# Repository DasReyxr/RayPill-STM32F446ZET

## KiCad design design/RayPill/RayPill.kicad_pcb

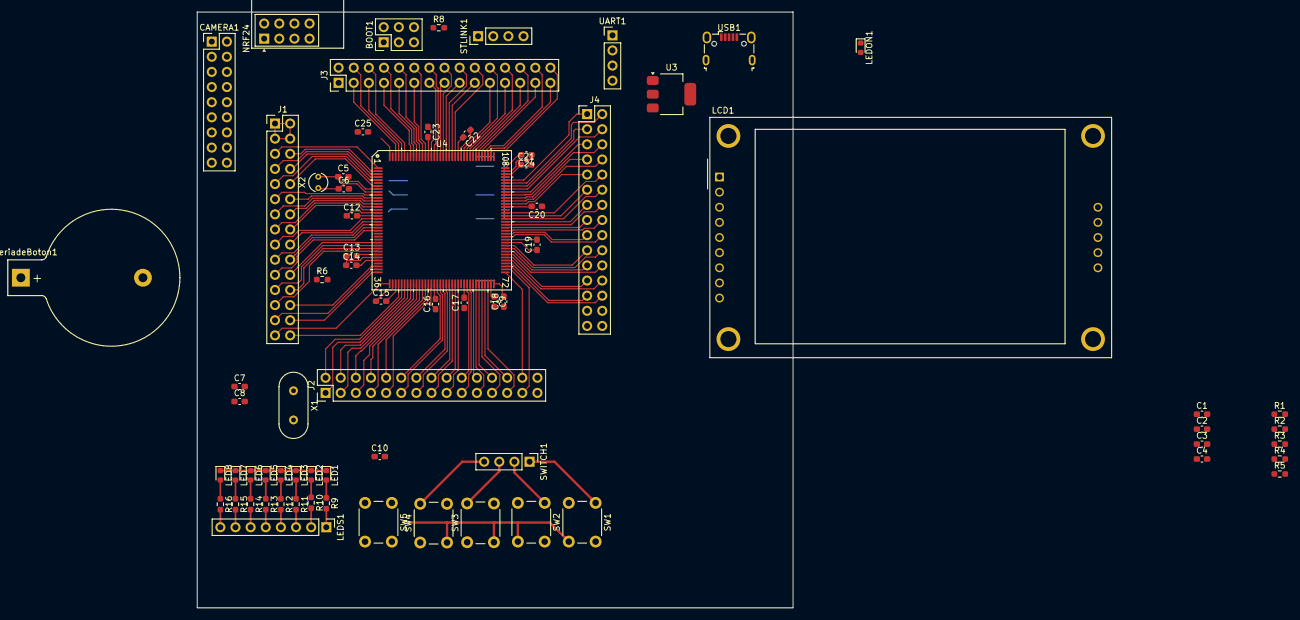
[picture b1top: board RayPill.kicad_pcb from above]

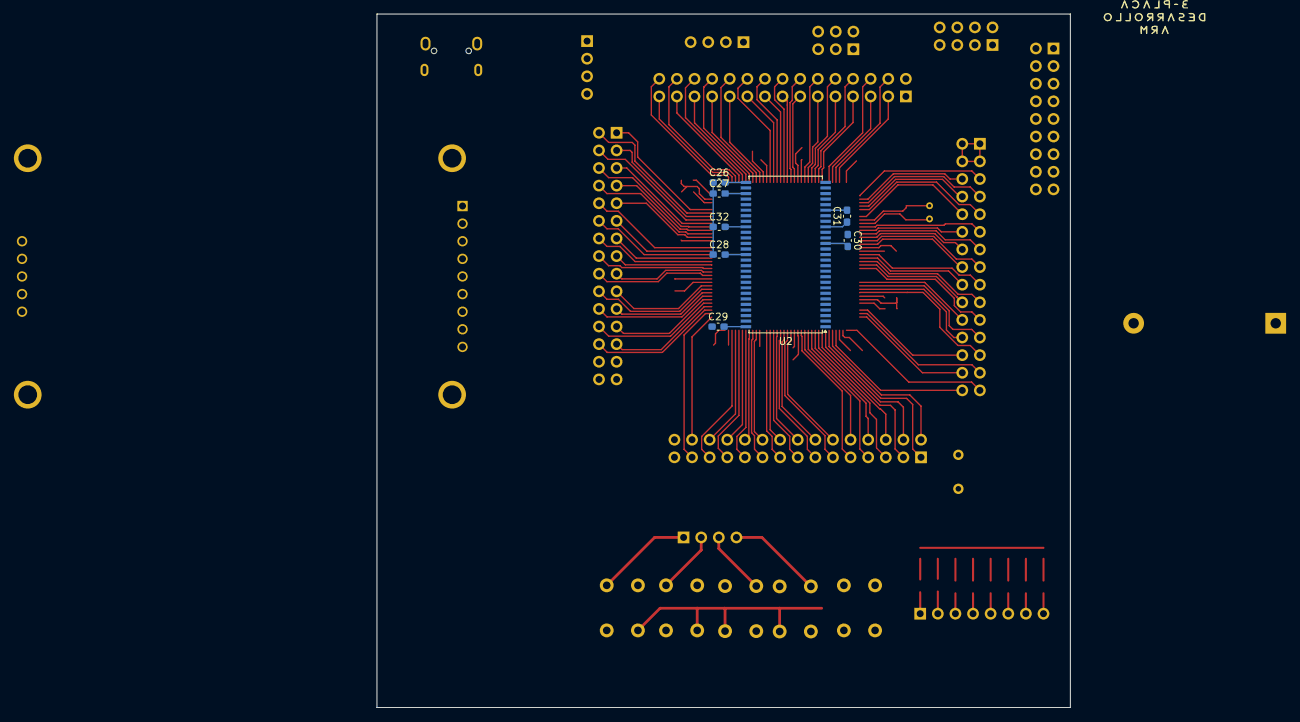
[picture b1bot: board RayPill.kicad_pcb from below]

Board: 2 copper layers, 100.0 x 100.0 mm, 80 parts (9 on the bottom side), 149 nets.

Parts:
BOOT1: Conn_02x03_Odd_Even; PinHeader_2x03_P2.54mm_Vertical
BateriadeBoton1: Portapila; BatteryHolder_Keystone_103_1x20mm
C1, C2: 10uF; C_0603_1608Metric_Pad1.08x0.95mm_HandSolder
C3, C4, C10, C12, C13, C14, C15, C16, C17, C18, C19, C20, C22, C23, C24, C25, C26, C27, C28, C29, C30, C31, C32: 100nF; C_0603_1608Metric_Pad1.08x0.95mm_HandSolder
C5, C6: 12p; C_0603_1608Metric_Pad1.08x0.95mm_HandSolder
C7, C8: 8p; C_0603_1608Metric_Pad1.08x0.95mm_HandSolder
C9: 2.2u; C_0603_1608Metric_Pad1.08x0.95mm_HandSolder
C21: 2.2uF; C_0603_1608Metric_Pad1.08x0.95mm_HandSolder
CAMERA1: Conn_02x09_Odd_Even; PinHeader_2x09_P2.54mm_Vertical
J1, J3, J4: Conn_02x15_Top_Bottom; PinHeader_2x15_P2.54mm_Vertical
J2: Conn_02x15_Odd_Even; PinHeader_2x15_P2.54mm_Vertical
LCD1: Conn_01x14; CR2013-MI2120
LED1, LED2, LED3, LED4, LED5, LED6, LED7, LED8: AZUL; LED_0603_1608Metric
LEDON1: ROJO; LED_0603_1608Metric
LEDS1: Conn_01x08; PinHeader_1x08_P2.54mm_Vertical
LOGO: LOGO; 3-LogoArm
NRF24: Conn_02x04_Odd_Even; nRF24L01_Breakout
R1, R2: 22; R_0603_1608Metric_Pad0.98x0.95mm_HandSolder
R3, R6, R8: 10k; R_0603_1608Metric_Pad0.98x0.95mm_HandSolder
R4, R9, R10, R11, R12, R13, R14, R15, R16: 220; R_0603_1608Metric_Pad0.98x0.95mm_HandSolder
R5: 0; R_0603_1608Metric_Pad0.98x0.95mm_HandSolder
STLINK1: Conn_01x04; PinHeader_1x04_P2.54mm_Vertical
SW1, SW2, SW3, SW4, SW5: SW_Push; SW_PUSH_6mm_H4.3mm
SWITCH1: Conn_01x04; PinHeader_1x04_P2.54mm_Vertical
U2: IS42S16400J-xT; TSOP-II-54_22.2x10.16mm_P0.8mm
U3: LM317_SOT-223; SOT-223-3_TabPin2
U4: STM32F446ZET7; LQFP-144_20x20mm_P0.5mm
UART1: Conn_01x04; PinHeader_1x04_P2.54mm_Vertical
USB1: USB_B_Mini; USB_Micro-B_Wuerth_629105150521
X1: 8MHz; Crystal_HC18-U_Vertical
X2: 32.768KHz; Crystal_C38-LF_D3.0mm_L8.0mm_Vertical

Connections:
+5V: C1.2, C3.2, R3.2, U3.3 (VI), USB1.1 (VBUS)
/28/U2: U2.28 (GND), U2.41 (GND), U2.54 (GND)
/33: R5.1, U4.33 (VDDA)
/BOOT0: BOOT1.3, U4.138 (BOOT0)
/BOOT1(PB2): J2.7, R8.2, U4.48 (PB2-BOOT1)
/PA0: J1.26, U4.34 (PA0-WKUP)
/PA1: J1.27, U4.35 (PA1)
/PA2: J1.28, U4.36 (PA2)
/PA3: J1.29, U4.37 (PA3)
/PA4: CAMERA1.6, J1.30, U4.40 (PA4)
/PA5: J2.2, LCD1.8, U4.41 (PA5)
/PA6: CAMERA1.7, J2.1, U4.42 (PA6)
/PA7: J2.4, LCD1.9, U4.43 (PA7)
/PA8: CAMERA1.8, J4.5, U4.100 (PA8)
/PA9: J4.4, U4.101 (PA9), UART1.2
/PA10: J4.3, U4.102 (PA10), UART1.3
/PA11: J4.2, U4.103 (PA11)
/PA12: J4.1, U4.104 (PA12)
/PA15: J3.30, U4.110 (PA15)
/PB0: J2.5, U4.46 (PB0)
/PB1: J2.8, U4.47 (PB1)
/PB3: J3.11, U4.133 (PB3)
/PB4: J3.10, LCD1.6, U4.134 (PB4)
/PB5: J3.9, U2.37 (CKE), U4.135 (PB5)
/PB6: J3.8, U2.19 (~CS), U4.136 (PB6)
/PB7: CAMERA1.5, J3.7, U4.137 (PB7)
/PB8: CAMERA1.3, J3.6, U4.139 (PB8)
/PB9: CAMERA1.4, J3.5, U4.140 (PB9)
/PB10: J2.26, U4.69 (PB10)
/PB11: J2.25, U4.70 (PB11)
/PB12: J2.28, U4.73 (PB12)
/PB13: J2.27, U4.74 (PB13)
/PB14: J4.26, R1.1, U4.75 (PB14)
/PB15: J4.25, R2.2, U4.76 (PB15)
/PC0: J1.22, U2.16 (~WE), U4.26 (PC0)
/PC1: J1.23, U4.27 (PC1)
/PC2: J1.24, U4.28 (PC2)
/PC3: J1.25, U4.29 (PC3)
/PC4: J2.3, U4.44 (PC4)
/PC5: J2.6, U4.45 (PC5)
/PC6: CAMERA1.16, J4.9, U4.96 (PC6)
/PC7: CAMERA1.15, J4.8, U4.97 (PC7)
/PC8: CAMERA1.14, J4.7, U4.98 (PC8)
/PC9: J4.6, U4.99 (PC9)
/PC10: J3.29, LCD1.5, NRF24.5, U4.111 (PC10)
/PC11: J3.28, LCD1.2, NRF24.7, U4.112 (PC11)
/PC12: J3.27, LCD1.3, NRF24.6, U4.113 (PC12)
/PC13: J1.10, U4.7 (PC13)
/PD0: J3.26, U2.5 (DQ2), U4.114 (PD0)
/PD1: J3.25, U2.7 (DQ3), U4.115 (PD1)
/PD2: J3.24, LCD1.12, U4.116 (PD2)
/PD3: CAMERA1.11, J3.23, U4.117 (PD3)
/PD4: J3.22, LCD1.11, U4.118 (PD4)
/PD5: J3.21, LCD1.10, U4.119 (PD5)
/PD6: J3.20, LCD1.7, U4.122 (PD6)
/PD7: J3.19, LCD1.4, U4.123 (PD7)
/PD8: J4.24, U2.50 (DQ13), U4.77 (PD8)
/PD9: J4.23, U2.51 (DQ14), U4.78 (PD9)
/PD10: J4.22, U2.53 (DQ15), U4.79 (PD10)
/PD11: J4.21, U4.80 (PD11)
/PD12: J4.20, U4.81 (PD12)
/PD13: J4.19, U4.82 (PD13)
/PD14: J4.18, U2.2 (DQ0), U4.85 (PD14)
/PD15: J4.17, U2.4 (DQ1), U4.86 (PD15)
/PE0: J3.4, U2.15 (LDQM), U4.141 (PE0)
/PE1: J3.3, U2.39 (UDQM), U4.142 (PE1)
/PE2: J1.5, U4.1 (PE2)
/PE3: J1.6, U4.2 (PE3)
/PE4: CAMERA1.12, J1.7, U4.3 (PE4)
/PE5: CAMERA1.10, J1.8, U4.4 (PE5)
/PE6: CAMERA1.9, J1.9, U4.5 (PE6)
/PE7: J2.15, U2.8 (DQ4), U4.58 (PE7)
/PE8: J2.18, U2.10 (DQ5), U4.59 (PE8)
/PE9: J2.17, U2.11 (DQ6), U4.60 (PE9)
/PE10: J2.20, U2.13 (DQ7), U4.63 (PE10)
/PE11: J2.19, U2.42 (DQ8), U4.64 (PE11)
/PE12: J2.22, U2.44 (DQ9), U4.65 (PE12)
/PE13: J2.21, U2.45 (DQ10), U4.66 (PE13)
/PE14: J2.24, U2.47 (DQ11), U4.67 (PE14)
/PE15: J2.23, U2.48 (DQ12), U4.68 (PE15)
/PF0: J1.11, U2.23 (A0), U4.10 (PF0)
/PF1: J1.12, U2.24 (A1), U4.11 (PF1)
/PF2: J1.13, U2.25 (A2), U4.12 (PF2)
/PF3: J1.14, U2.26 (A3), U4.13 (PF3)
/PF4: J1.15, U2.29 (A4), U4.14 (PF4)
/PF5: J1.16, U2.30 (A5), U4.15 (PF5)
/PF6: J1.17, U4.18 (PF6)
/PF7: J1.18, U4.19 (PF7)
/PF8: J1.19, U4.20 (PF8)
/PF9: J1.20, U4.21 (PF9)
/PF10: J1.21, U4.22 (PF10)
/PF11: J2.10, U2.18 (~RAS), U4.49 (PF11)
/PF12: J2.9, U2.31 (A6), U4.50 (PF12)
/PF13: J2.12, U2.32 (A7), U4.53 (PF13)
/PF14: J2.11, U2.33 (A8), U4.54 (PF14)
/PF15: J2.14, U2.34 (A9), U4.55 (PF15)
/PG0: J2.13, U2.22 (A10), U4.56 (PG0)
/PG1: J2.16, U2.35 (A11), U4.57 (PG1)
/PG2: J4.16, U4.87 (PG2)
/PG3: J4.15, U4.88 (PG3)
/PG4: J4.14, U2.20 (BA0), U4.89 (PG4)
/PG5: J4.13, U2.21 (BA1), U4.90 (PG5)
/PG6: J4.12, U4.91 (PG6)
/PG7: J4.11, U4.92 (PG7)
/PG8: J4.10, U2.38 (CLK), U4.93 (PG8)
/PG9: J3.18, LCD1.1, U4.124 (PG9)
/PG10: J3.17, NRF24.3, U4.125 (PG10)
/PG11: CAMERA1.13, J3.16, U4.126 (PG11)
/PG12: J3.15, NRF24.4, U4.127 (PG12)
/PG13: J3.14, NRF24.8, U4.128 (PG13)
/PG14: J3.13, U4.129 (PG14)
/PG15: J3.12, U2.17 (~CAS), U4.132 (PG15)
/RES: C10.2, R6.2, SW5.2, U4.25 (NRST)
/SWCLK: STLINK1.2, U4.109 (PA14)
/SWDIO: STLINK1.3, U4.105 (PA13)
/VBAT: BateriadeBoton1.1, U4.6 (VBAT)
Earth: BateriadeBoton1.2, C1.1, C2.1, C3.1, C4.1, LCD1.13, LEDON1.1 (K), STLINK1.4, U3.1 (ADJ), UART1.4, USB1.5 (GND)
GND: BOOT1.5, BOOT1.6, C5.2, C6.2, C7.2, C8.2, C9.2, C10.1, C12.1, C13.1, C14.1, C15.1, C16.1, C17.1, C18.1, C19.1, C20.1, C21.2, C22.1, C23.1, C24.1, C25.1, C26.1, C27.1, C28.1, C29.1, C30.1, C31.1, C32.1, CAMERA1.2, J2.29, J2.30, J4.27, J4.28, J4.29, J4.30, LED1.1 (K), LED2.1 (K), LED3.1 (K), LED4.1 (K), LED5.1 (K), LED6.1 (K), LED7.1 (K), LED8.1 (K), NRF24.1, SW1.2, SW2.2, SW3.2, SW4.2, SW5.1, U2.6 (GNDQ), U2.12 (GNDQ), U2.46 (GNDQ), U2.52 (GNDQ), U4.16 (VSS), U4.31 (VSSA), U4.38 (VSS), U4.51 (VSS), U4.61 (VSS), U4.83 (VSS), U4.94 (VSS), U4.107 (VSS), U4.120 (VSS), U4.130 (VSS)
unnamed: BOOT1.4, R8.1
unnamed: LED1.2 (A), R9.1
unnamed: LED2.2 (A), R10.1
unnamed: LED3.2 (A), R11.1
unnamed: LED4.2 (A), R12.1
unnamed: LED5.2 (A), R13.1
unnamed: LED6.2 (A), R14.1
unnamed: LED7.2 (A), R15.1
unnamed: LED8.2 (A), R16.1
unnamed: LEDON1.2 (A), R4.2
unnamed: LEDS1.1, R9.2
unnamed: LEDS1.2, R10.2
unnamed: LEDS1.3, R11.2
unnamed: LEDS1.4, R12.2
unnamed: LEDS1.5, R13.2
unnamed: LEDS1.6, R14.2
unnamed: LEDS1.7, R15.2
unnamed: LEDS1.8, R16.2
unnamed: SW1.1, SWITCH1.1
unnamed: SW2.1, SWITCH1.2
unnamed: SW3.1, SWITCH1.3
unnamed: SW4.1, SWITCH1.4
unnamed: C5.1, U4.8 (PC14-OSC32_IN), X2.2
unnamed: C6.1, U4.9 (PC15-OSC32_OUT), X2.1
unnamed: C7.1, U4.23 (PH0-OSC_IN), X1.2
unnamed: C8.1, U4.24 (PH1-OSC_OUT), X1.1
unnamed: C9.1, U4.71 (VCAP_1)
unnamed: C21.1, U4.106 (VCAP_2)
unnamed: R2.1, R3.1, USB1.3 (D+)
unnamed: R1.2, USB1.2 (D-)
VDD: BOOT1.1, BOOT1.2, C2.2, C4.2, C12.2, C13.2, C14.2, C15.2, C16.2, C17.2, C18.2, C19.2, C20.2, C22.2, C23.2, C24.2, C25.2, C26.2, C27.2, C28.2, C29.2, C30.2, C31.2, C32.2, CAMERA1.1, J1.1, J1.2, J1.3, J1.4, J3.1, J3.2, LCD1.14, NRF24.2, R4.1, R5.2, R6.1, STLINK1.1, U2.1 (VDD), U2.3 (VDDQ), U2.9 (VDDQ), U2.14 (VDD), U2.27 (VDD), U2.43 (VDDQ), U2.49 (VDDQ), U3.2 (VO), U4.17 (VDD), U4.30 (VDD), U4.32 (VREF+), U4.39 (VDD), U4.52 (VDD), U4.62 (VDD), U4.72 (VDD), U4.84 (VDD), U4.95 (VDDUSB), U4.108 (VDD), U4.121 (VDD), U4.131 (VDD), U4.144 (VDD), UART1.1
